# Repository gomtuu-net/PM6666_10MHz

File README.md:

# 10MHz OCXO for Philips/Fluke PM6666 counter
Alternative 10MHz oscillator for Philips/Fluke PM6665 and PM6666 frequency counters.

[Schematic](https://github.com/gomtuu-net/PM6666_10MHz/blob/master/PM6666-10MHz.pdf)

[Created with KiCAD ver. 7.0.11](https://kicad.org)

## Design ideas
* fuse/PTCC
* Vref with trim-pot for fine tune (Vc xtal: 0-4V)
* DC-DC conv (12V-to-5V)
* LCD-backlight power & trim-pot
* jumper to choose always-on or power-switch 
* SMA and Vref test-point
* 4 mount holes for alternative use
* status LED after fuse/DC-DC conv.
- temp.sensor under/near OCXO (LM35/DS18b20)
- Window-comparator with warm/cold LED indicator
- filter/circuit to convert square to sine-wave
- freq. divider
* currently usable OCXO: CTI OSC5A2B02 / NDK ENE3311B
- allow multiple footprints to fit other OCXO (ISOtemp/Vectron)

## Issues/todo
- Pk-Pk voltage from OCXO to high, need 470 load resistor
- change diameter hole for OCXO (0.8mm is to narrow)
- update/correct footprint thp Elco's (47uF & 100uF)
- improv. Vref tuning (20-turn trim-pot?)
- add solder-jumper to seperate 10MHz signal (antenne!)
- power-on LED at better location
- update part marking (pin.1, +, etc)

MHz.kHz.Hz
010.000.000
123.456.789

## Possible voltage references
- ADR4540		4.096V	2ppm	Vin: 4.2 - 15V
* LM4140		4.096V	3ppm	Vin: 5V
- LT1019-5		5.000V	5ppm
- LT1021		5.000V	5ppm	Vin: >10V
- MAX874		4.096V	20ppm	Vin: 4.3 - 20V
- MAX6070AAUT	4.096V	6ppm	Vin: 4.3 - 5.5V
- MAX6194A		4.500V	5ppm	Vin: 5 - 12.6V
* MAX6198A		4.096V	2ppm	Vin: 5 - 12.6V
- MAX6241		4.096V	5ppm	Vin: 8 - 36V
- MAX6341		4.096V	2.5ppm	Vin: 8 - 36V
- MAX6250BESA	5.000V	7ppm	
- REF5040		4.096V	3ppm	Vin: 4.3 - 18V

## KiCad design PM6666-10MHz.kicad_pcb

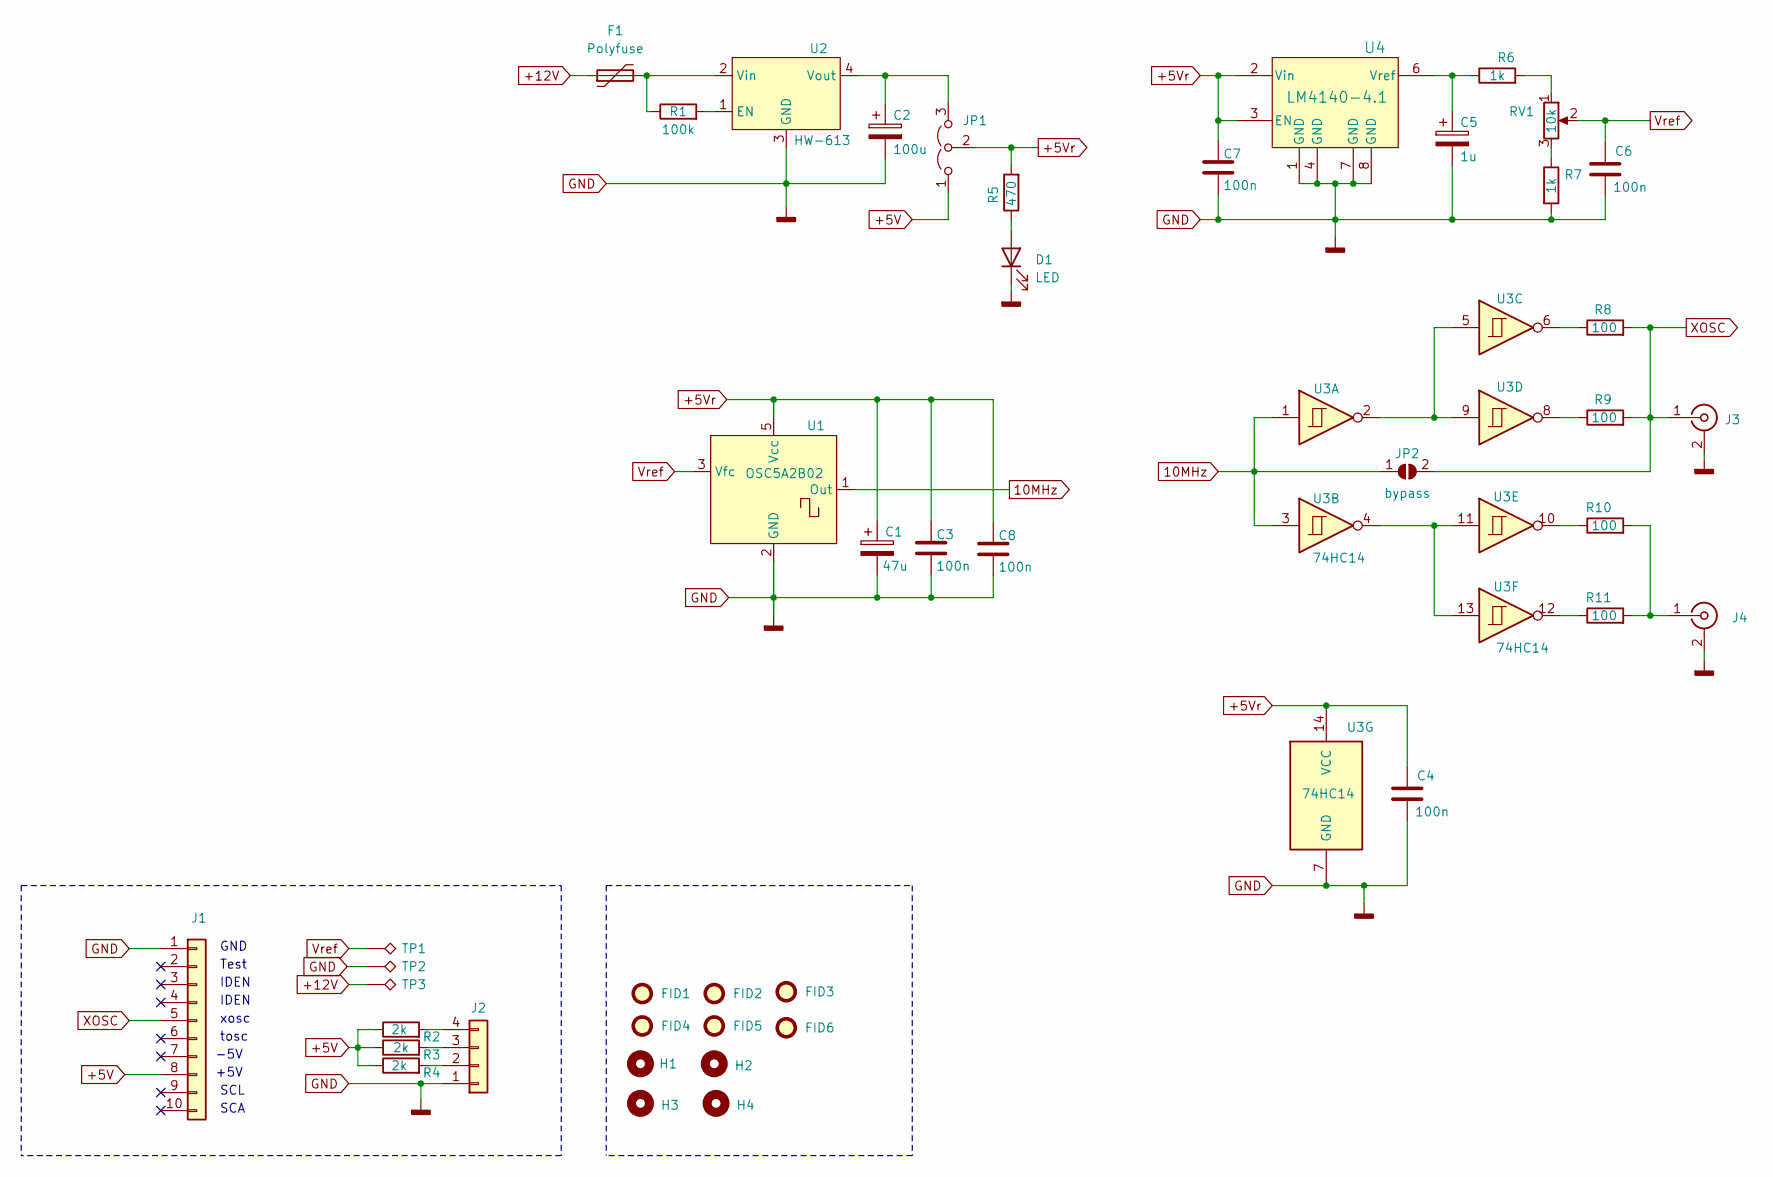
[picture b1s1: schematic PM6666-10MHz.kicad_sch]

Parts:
C1: 47u; CP_Radial_D4.0mm_P2.00mm
C2: 100u; CP_Radial_D4.0mm_P2.00mm
C3, C4, C6, C7, C8: 100n; C_1206_3216Metric_Pad1.33x1.80mm_HandSolder
C5: 1u; C_1206_3216Metric_Pad1.33x1.80mm_HandSolder
D1: LED; LED_1206_3216Metric_Pad1.42x1.75mm_HandSolder
F1: Polyfuse; Fuse_Littelfuse_395Series
FID1, FID2, FID3, FID4, FID5, FID6: Fiducial; Fiducial_0.5mm_Mask1.5mm
H1, H2, H3, H4: MountingHole; MountingHole_3.2mm_M3
J1: JST_EH_B10B-EH-A_1x10_P2.50mm_Vertical
J2: PinHeader_1x04_P2.54mm_Vertical
J3, J4: Conn_Coaxial; SMA_Amphenol_901-144_Vertical
JP1: PinHeader_1x03_P2.54mm_Vertical
JP2: bypass; SolderJumper-2_P1.3mm_Open_RoundedPad1.0x1.5mm
R1: 100k; R_1206_3216Metric_Pad1.30x1.75mm_HandSolder
R2, R3, R4: 2k; R_1206_3216Metric_Pad1.30x1.75mm_HandSolder
R5: 470; R_1206_3216Metric_Pad1.30x1.75mm_HandSolder
R6, R7: 1k; R_1206_3216Metric_Pad1.30x1.75mm_HandSolder
R8, R9, R10, R11: 100; R_1206_3216Metric_Pad1.30x1.75mm_HandSolder
RV1: 10k; Potentiometer_Bourns_3296Z_Horizontal
TP1: Vref; TestPoint_Loop_D1.80mm_Drill1.0mm_Beaded
TP2: GND; TestPoint_Loop_D1.80mm_Drill1.0mm_Beaded
TP3: +12V; TestPoint_Loop_D1.80mm_Drill1.0mm_Beaded
U1: OSC5A2B02; Oscillator_OCXO_OSC5A2B02
U2: HW-613; Convertor_DCDC_HW-613
U3: 74HC14; SO-14_3.9x8.65mm_P1.27mm
U4: LM4140-4.1; SOIC-8_3.9x4.9mm_P1.27mm

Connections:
10MHz: JP2.1 (A), U1.1 (Out), U3.1, U3.3
+5V: J1.8, JP1.1 (A), R2.1, R3.1, R4.1
+5Vr: C1.1, C3.1, C4.1, C7.1, C8.1, JP1.2 (C), R5.2, U1.5 (Vcc), U3.14 (VCC), U4.2 (Vin), U4.3 (EN)
+12V: F1.1, TP3.1
GND: C1.2, C2.2, C3.2, C4.2, C5.2, C6.2, C7.2, C8.2, D1.1 (K), J1.1, J2.1, J3.2 (Ext), J4.2 (Ext), R7.2, TP2.1, U1.2 (GND), U2.3 (GND), U3.7 (GND), U4.1 (GND), U4.4 (GND), U4.7 (GND), U4.8 (GND)
unnamed: D1.2 (A), R5.1
unnamed: J2.2, R4.2
unnamed: J2.3, R3.2
unnamed: J2.4, R2.2
unnamed: J4.1 (In), R10.2, R11.2
unnamed: C2.1, JP1.3 (B), U2.4 (Vout)
unnamed: R6.2, RV1.1
unnamed: R7.1, RV1.3
unnamed: R8.1, U3.6
unnamed: R9.1, U3.8
unnamed: R10.1, U3.10
unnamed: R11.1, U3.12
unnamed: R1.2, U2.1 (EN)
unnamed: F1.2, R1.1, U2.2 (Vin)
unnamed: U3.2, U3.5, U3.9
unnamed: U3.4, U3.11, U3.13
unnamed: C5.1, R6.1, U4.6 (Vref)
Vref: C6.1, RV1.2, TP1.1, U1.3 (Vfc)
XOSC: J1.5, J3.1 (In), JP2.2 (B), R8.2, R9.2

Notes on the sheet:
xosc
IDEN
SCL
tosc
GND
+5V
Test
SCA
-5V

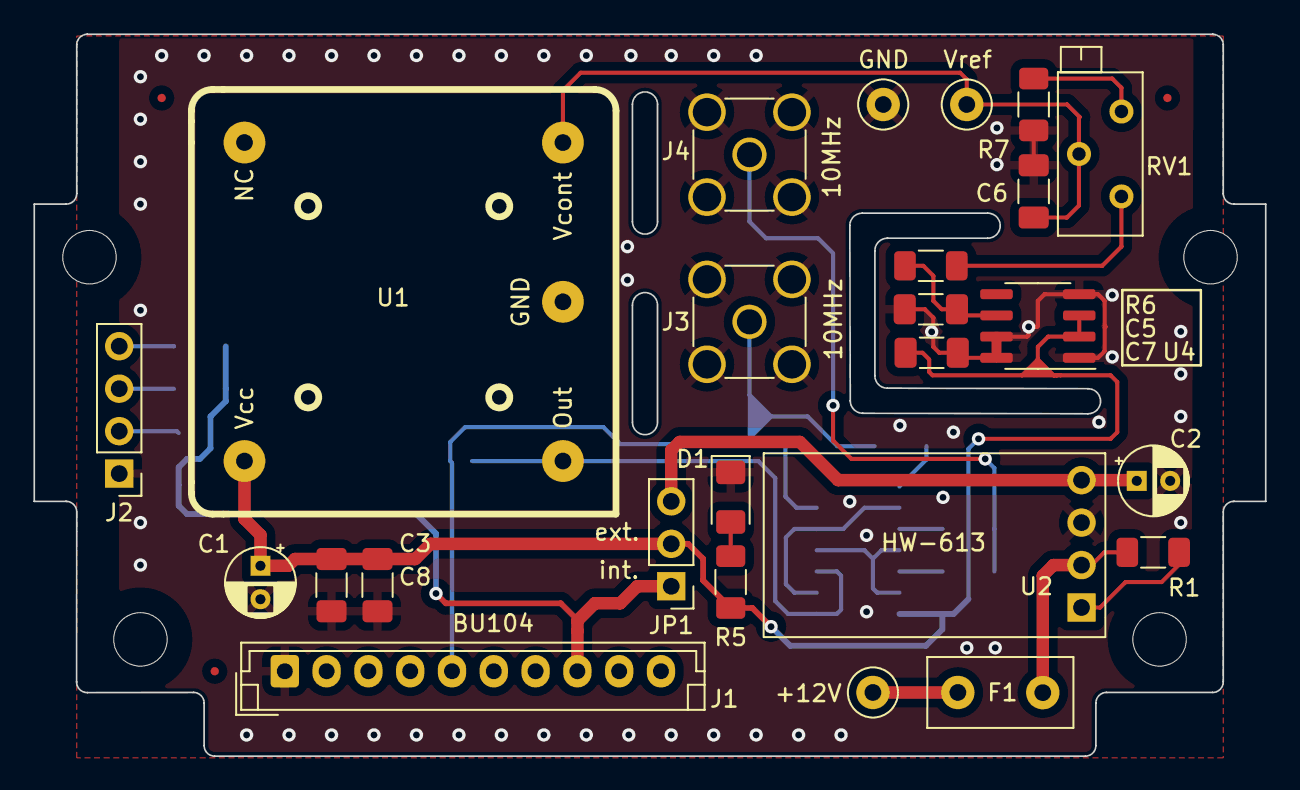
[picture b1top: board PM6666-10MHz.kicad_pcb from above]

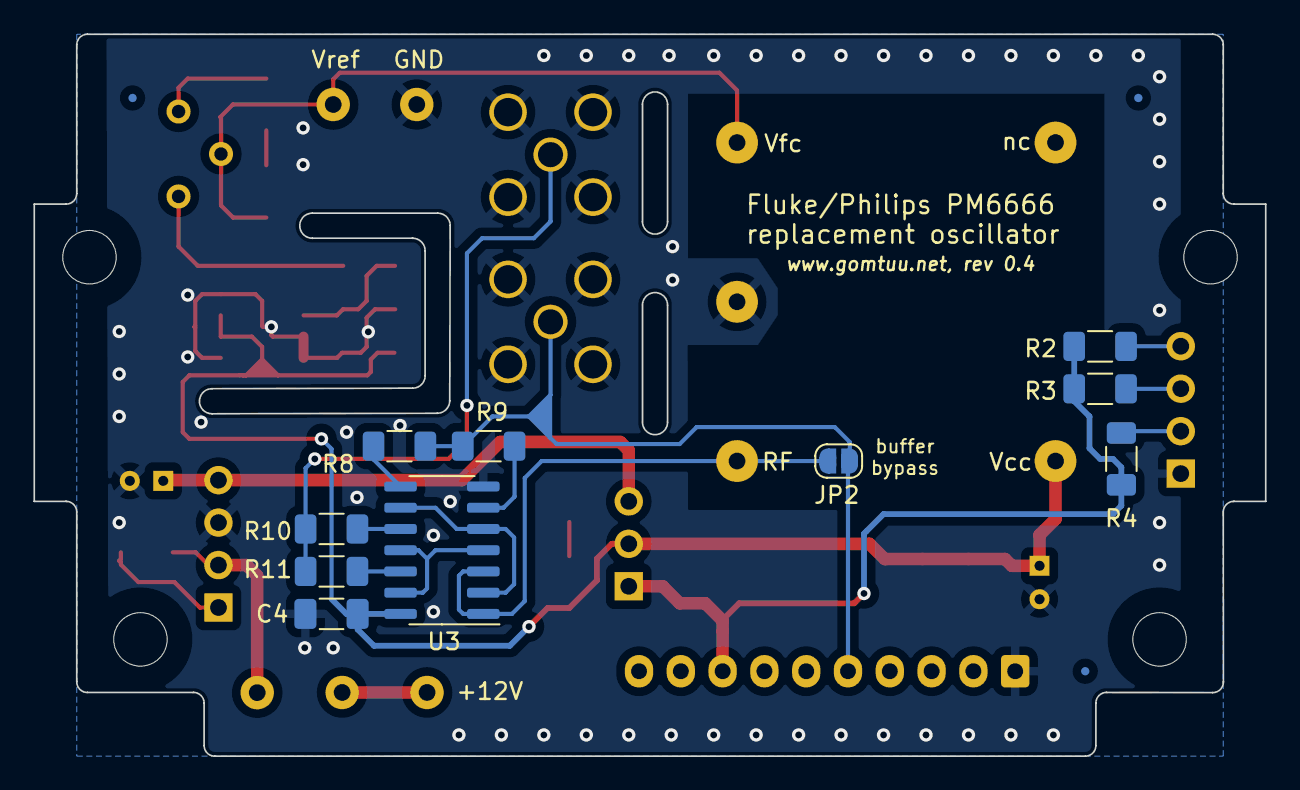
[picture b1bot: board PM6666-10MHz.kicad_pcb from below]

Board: 2 copper layers, 73.7 x 43.2 mm, 45 parts (13 on the bottom side), 24 nets.

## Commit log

2024-11-09 Add files via upload
    Initial commit.
2024-11-11 Add files via upload
    Adding schematic in PDF format
2024-11-11 Add files via upload
    Adding 3D view of the final PCB
